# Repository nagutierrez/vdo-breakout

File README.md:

# VDO Breakout

A 4-gauge breakout board for VDO automotive instruments (e.g. Vision Black), with fused 12 V distribution, sender signal routing, and PWM dimming for LED backlighting.

## Overview

VDO gauges (e.g. Vision Black) terminate in **4–5 individual spade connectors**, not a single harness plug: **2 or 3 for the gauge** (12v power, ground, and usually a sender/sense) plus **2 for the bulb** (Light+, Light−). Wiring these directly in a custom dash in place is tedious.

This board consolidates those spade connections into four gauge ports (Molex Micro-Fit) plus dedicated power and signal headers — one harness per gauge instead of a handful of loose spades.

**LED backlighting** does not dim with a stock rheostat alone. An **ATtiny402** reads the vehicle dimmer input and PWM-switches the shared **Light−** return via an **IRLML2502** MOSFET so LED backlights track the dash lighting level.

```mermaid
flowchart LR
  Rheostat["Vehicle rheostat"] --> ADC["ATtiny402 ADC"]
  ADC --> PWM["PWM output"]
  PWM --> MOSFET["Q1 MOSFET"]
  MOSFET --> LightMinus["Gauge Light−"]
  Ign12V["Ignition 12V"] --> Gauges["4× gauge connectors"]
  Gauges --> SenseHeader["Signals header"]
```

## Features

- Individual Molex Micro-Fit 3.0 connectors for each gauge (J3–J6)
- Power input protection with mini blade fuse + 15 V TVS
- Single connector for all 4 gauge sender signals (J2)
- Rheostat input on power connector (J1)
- ATtiny402 PWM dimming on shared Light− (enables LED backlighting with rheostat-following brightness)
- UPDI programming header (J7); KiCad sources + production files in [`hardware/`](hardware/)

### Gauge connectors J3–J6

Molex 43650-0515 (one per gauge). PCB silk: `L−  L+  GND  12V  S^N`

| Pin | Signal |
| --- | ------ |
| 1 | Sense (sender) |
| 2 | +12V (ignition-switched gauge power) |
| 3 | GND |
| 4 | Light+ |
| 5 | Light− (PWM-switched) |

J3 = Gauge 1 … J6 = Gauge 4.

### Power J1

Molex 43650-0300

| Pin | Signal |
| --- | ------ |
| 1 | Lighting rheostat |
| 2 | GND |
| 3 | Ignition 12V |

### Dimming

Rheostat-following dimming on J1 pin 1 only works when the vehicle dimmer is wired **high-side** — the rheostat sits between the lighting supply and the bulbs. Brightness increases as voltage on pin 1 rises.

If the stock dimmer is **low-side** (between bulbs and ground), do not connect it to J1 for dimming. The voltage is inverted (full brightness ≈ 0 V, dimmest ≈ supply voltage) and indistinguishable at 0 V, where both full brightness and lights-off read ~0 V.

For low-side vehicles, add a separate potentiometer near the board, wired as a high-side divider between the lighting supply and J1 pin 1 (with GND on J1 pin 2), to dim the gauge backlights independently of the stock dash dimmer.

### Signals J2

Molex 43650-0400

| Pin | Signal |
| --- | ------ |
| 1 | Sense 1 |
| 2 | Sense 2 |
| 3 | Sense 3 |
| 4 | Sense 4 |

### Program J7

2.54 mm pin header

| Pin | Signal |
| --- | ------ |
| 1 | UPDI |
| 2 | GND |
| 3 | +5V |

## Building the board

- Open design: [`hardware/VDO Breakout.kicad_pro`](hardware/VDO%20Breakout.kicad_pro) (KiCad 10)
- BOM: [`hardware/production/bom.csv`](hardware/production/bom.csv) (LCSC part numbers included)
- Gerbers: [`hardware/production/VDO_Breakout.zip`](hardware/production/VDO_Breakout.zip)
- Pick-and-place: [`hardware/production/positions.csv`](hardware/production/positions.csv)

Open items:

- Fuse rating (F1) is not specified in the BOM — choose based on total gauge load.
- LDO is listed as HT75xx; confirm 5 V variant when ordering.

## Firmware

PlatformIO project in [`firmware/`](firmware/). The **ATtiny402** reads the vehicle dimmer on **PA6** (ADC) and PWM-switches gauge Light− on **PA1**.

Two build profiles: `ATtiny402` (incandescent fade timings) and `ATtiny402_LED` (faster fades for LED backlights). Program via UPDI on J7 — see the [firmware README](firmware/README.md) for build and flash instructions.

## Repository layout

```
hardware/     KiCad schematic, PCB, and production outputs
firmware/     ATtiny402 dimming firmware (PlatformIO)
```

## License

- **Hardware** ([`hardware/`](hardware/)): [CC BY-NC-SA 4.0](https://creativecommons.org/licenses/by-nc-sa/4.0/) — non-commercial use; derivatives must use the same license.
- **Firmware** ([`firmware/`](firmware/)): [MIT](firmware/LICENSE)

See [LICENSE.md](LICENSE.md) for details.

## Disclaimer

This is an automotive electrical project. Use at your own risk. Verify all wiring against your vehicle and gauge documentation before connecting power.

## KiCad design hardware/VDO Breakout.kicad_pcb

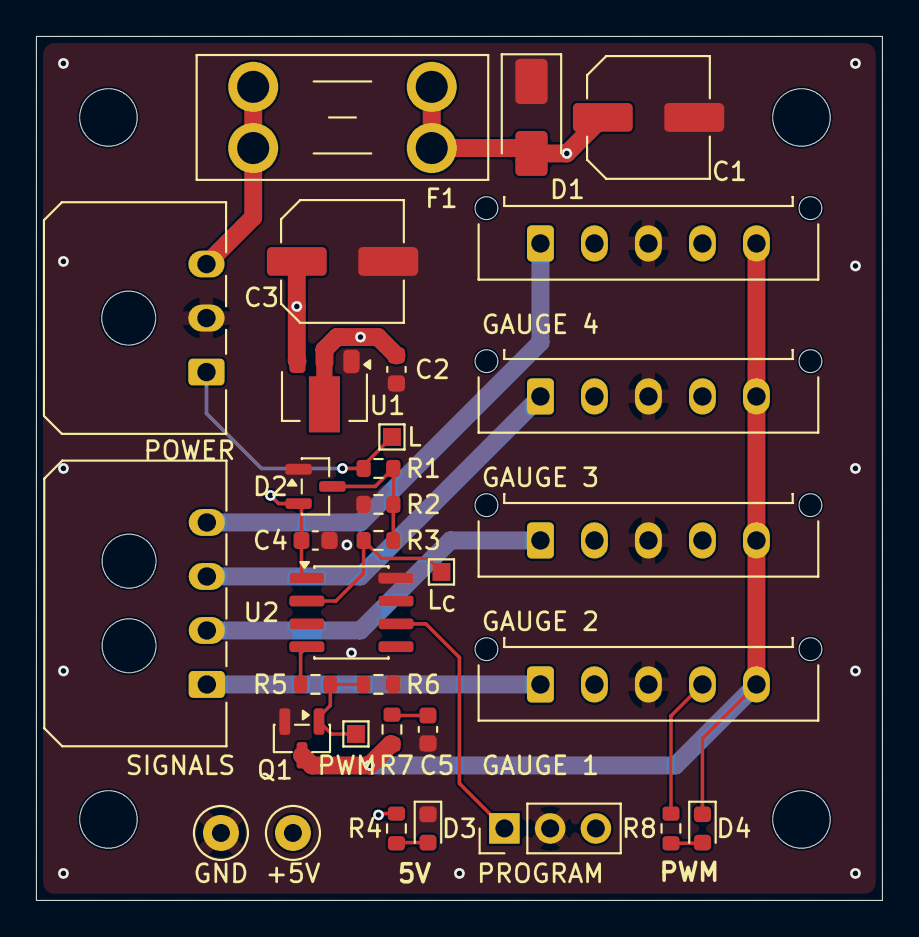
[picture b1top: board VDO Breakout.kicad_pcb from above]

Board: 4 copper layers, 47.0 x 48.0 mm, 37 parts (0 on the bottom side), 18 nets.

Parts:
C1, C3: 100uF; C_Elec_6.3x7.7
C2, C4: 100nF; C_0603_1608Metric
C5: 10nF; C_0603_1608Metric
D1: SMAJ15CA; D_SMA
D2: BAV99; SOT-23
D3, D4: LED; LED_0603_1608Metric
F1: Fuse; Fuseholder_Blade_Mini_Keystone_3568
H1, H2, H3, H4: MountingHole; MountingHole_3.2mm_M3
J1: POWER; Molex_Micro-Fit_3.0_43650-0300_1x03_P3.00mm_Horizontal
J2: SIGNALS; Molex_Micro-Fit_3.0_43650-0400_1x04_P3.00mm_Horizontal
J3: GAUGE 1; Molex_Micro-Fit_3.0_43650-0515_1x05_P3.00mm_Vertical
J4: GAUGE 2; Molex_Micro-Fit_3.0_43650-0515_1x05_P3.00mm_Vertical
J5: GAUGE 3; Molex_Micro-Fit_3.0_43650-0515_1x05_P3.00mm_Vertical
J6: GAUGE 4; Molex_Micro-Fit_3.0_43650-0515_1x05_P3.00mm_Vertical
J7: PROGRAM; PinHeader_1x03_P2.54mm_Vertical
Q1: IRLML2502; SOT-23
R1: 10k; R_0603_1608Metric
R2: 6k8; R_0603_1608Metric
R3, R5: 1k; R_0603_1608Metric
R4: 3k3; R_0603_1608Metric
R6: 100k; R_0603_1608Metric
R7: 100; R_0603_1608Metric
R8: 4k7; R_0603_1608Metric
TP1: PWM; TestPoint_Pad_1.0x1.0mm
TP2: L; TestPoint_Pad_1.0x1.0mm
TP3: L_{C}; TestPoint_Pad_1.0x1.0mm
TP4: +5V; TestPoint_Loop_D2.50mm_Drill1.0mm
TP5: GND; TestPoint_Loop_D2.50mm_Drill1.0mm
U1: HT75xx-1-SOT89; SOT-89-3
U2: ATtiny402-SS; SOIC-8_3.9x4.9mm_P1.27mm

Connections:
+5V: C3.1, C4.2, D2.2 (A), J7.3, R4.1, TP4.1 (1_1), U1.3 (VOUT), U2.1 (VCC)
+12V: C1.1, C2.1, D1.2 (A2), F1.2, J3.2, J3.4, J4.2, J4.4, J5.2, J5.4, J6.2, J6.4, R8.1, U1.2 (VIN)
/Ign Power: F1.1, J1.3
/Light-: D4.1 (K), J3.5, J4.5, J5.5, J6.5, Q1.3 (D), R7.1
/Lighting_{Conditioned}: R3.2, TP3.1 (1_1), U2.2 (PA6)
/Lighting_{Raw}: J1.1, R1.1, TP2.1 (1_1)
/PWM: R5.1, U2.4 (PA1)
/Sense^{1}: J2.1, J3.1
/Sense^{2}: J2.2, J4.1
/Sense^{3}: J2.3, J5.1
/Sense^{4}: J2.4, J6.1
/UPDI: J7.1, U2.6 (~RESET/PA0)
GND: C1.2, C2.2, C3.2, C4.1, C5.1, D1.1 (A1), D2.1 (K), D3.1 (K), J1.2, J3.3, J4.3, J5.3, J6.3, J7.2, Q1.2 (S), R2.2, R6.2, TP5.1 (1_1), U1.1 (GND), U2.8 (GND)
unnamed: C5.2, R7.2
unnamed: D2.3 (K), R1.2, R2.1, R3.1
unnamed: D3.2 (A), R4.2
unnamed: D4.2 (A), R8.2
unnamed: Q1.1 (G), R5.2, R6.1, TP1.1 (1_1)

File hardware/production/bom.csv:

Designator,Footprint,Quantity,Value,LCSC Part #
"C1, C3",C_Elec_6.3x7.7,2,100uF,C3035877
"C2, C4",0603,2,100nF,C14663
C5,0603,1,10nF,C57112
D1,D_SMA,1,SMAJ15CA,C19077536
D2,SOT-23,1,BAV99,C2500 
"D3, D4",0603,2,LED,C2286 
F1,Fuseholder_Blade_Mini_Keystone_3568,1,Fuse,
J1,Molex_Micro-Fit_3.0_43650-0300_1x03_P3.00mm_Horizontal,1,POWER,
J2,Molex_Micro-Fit_3.0_43650-0400_1x04_P3.00mm_Horizontal,1,SIGNALS,
J3,Molex_Micro-Fit_3.0_43650-0515_1x05_P3.00mm_Vertical,1,GAUGE 1,
J4,Molex_Micro-Fit_3.0_43650-0515_1x05_P3.00mm_Vertical,1,GAUGE 2,
J5,Molex_Micro-Fit_3.0_43650-0515_1x05_P3.00mm_Vertical,1,GAUGE 3,
J6,Molex_Micro-Fit_3.0_43650-0515_1x05_P3.00mm_Vertical,1,GAUGE 4,
J7,PinHeader_1x03_P2.54mm_Vertical,1,PROGRAM,
Q1,SOT-23,1,IRLML2502,C2589 
R1,0603,1,10k,C25804
R2,0603,1,6k8,C23212
"R3, R5",0603,2,1k,C21190
R4,0603,1,3k3,C22978
R6,0603,1,100k,C25803
R7,0603,1,100,C22775
R8,0603,1,4k7,C23162
TP4,TestPoint_Loop_D2.50mm_Drill1.0mm,1,+5V,
TP5,TestPoint_Loop_D2.50mm_Drill1.0mm,1,GND,
U1,SOT-89-3,1,HT75xx-1-SOT89,C16106
U2,SOIC-8_3.9x4.9mm_P1.27mm,1,ATtiny402-SS,C2053235

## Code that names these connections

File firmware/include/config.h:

#pragma once

#include <Arduino.h>

// PA6: conditioned 0-5 V dimmer input. PA1: PWM to MOSFET gate. PA0: UPDI only.
constexpr uint8_t PIN_ADC = PIN_PA6;
constexpr uint8_t PIN_PWM = PIN_PA1;

// Hysteresis thresholds on 10-bit ADC counts (~2% / ~4% of full scale).
constexpr uint16_t ADC_OFF_THRESHOLD = 20;
constexpr uint16_t ADC_ON_THRESHOLD = 41;

// Map usable dimmer range to PWM duty; tune on bench if needed.
constexpr uint16_t ADC_MIN = 20;
constexpr uint16_t ADC_MAX = 1000;

constexpr uint8_t ADC_EMA_SHIFT = 4;

constexpr uint16_t SIGNAL_OFF_DEBOUNCE_MS = 100;
constexpr uint16_t LOOP_INTERVAL_MS = 20;

// Force PWM off when supply sags during capacitor discharge on power cut.
constexpr uint16_t VDD_SHUTDOWN_MV = 4500;

#ifndef LOAD_PROFILE_INCANDESCENT
#ifndef LOAD_PROFILE_LED
#define LOAD_PROFILE_INCANDESCENT
#endif
#endif

#if defined(LOAD_PROFILE_LED)
constexpr uint16_t FADE_IN_MS = 300;
constexpr uint16_t FADE_OUT_MS = 200;
#else
constexpr uint16_t FADE_IN_MS = 1500;
constexpr uint16_t FADE_OUT_MS = 500;
#endif

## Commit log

2026-06-17 Initial commit; hardware and project structure
2026-06-17 Add initial implementation of firmware
2026-06-17 Add ATtiny402 gauge dimming firmware with LED/incandescent profiles and brownout protection.
2026-06-17 Add licensing information
2026-06-17 Remove unecessary and vaguely incorrect documentation, add iamge of assembled board
2026-06-21 Add note about low side dimmers not being compatible
